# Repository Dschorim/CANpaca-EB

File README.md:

# CANpaca-EB
This is the extruder board from the CANpaca printer board family.

## Features
 - CAN input (with 7.5A@24V) input
 - 1 extrudder stepper (via tmc2130 with SPI control)
 - 2 PWM fans
 - support for klicky probe / bltouch
 - 1 hotend
 - 1 regular thermistor
 - 1 thermistor via MAX31865
 - ADXL345 Accererometer
 - runout sensor
 - RGB lighting

## Changelog

### V0.2
 - changed caps from 0603 to 0402
 - changed resistors from 0603 to 0402
 - decoupling caps are now properly placed close to power pins
 - added thermal vias below rp2040
 - increased via diameter from 0.4mm to 0.45mm to save cost
 - changed to hardware SPI pins

### V0.1
 - initial release

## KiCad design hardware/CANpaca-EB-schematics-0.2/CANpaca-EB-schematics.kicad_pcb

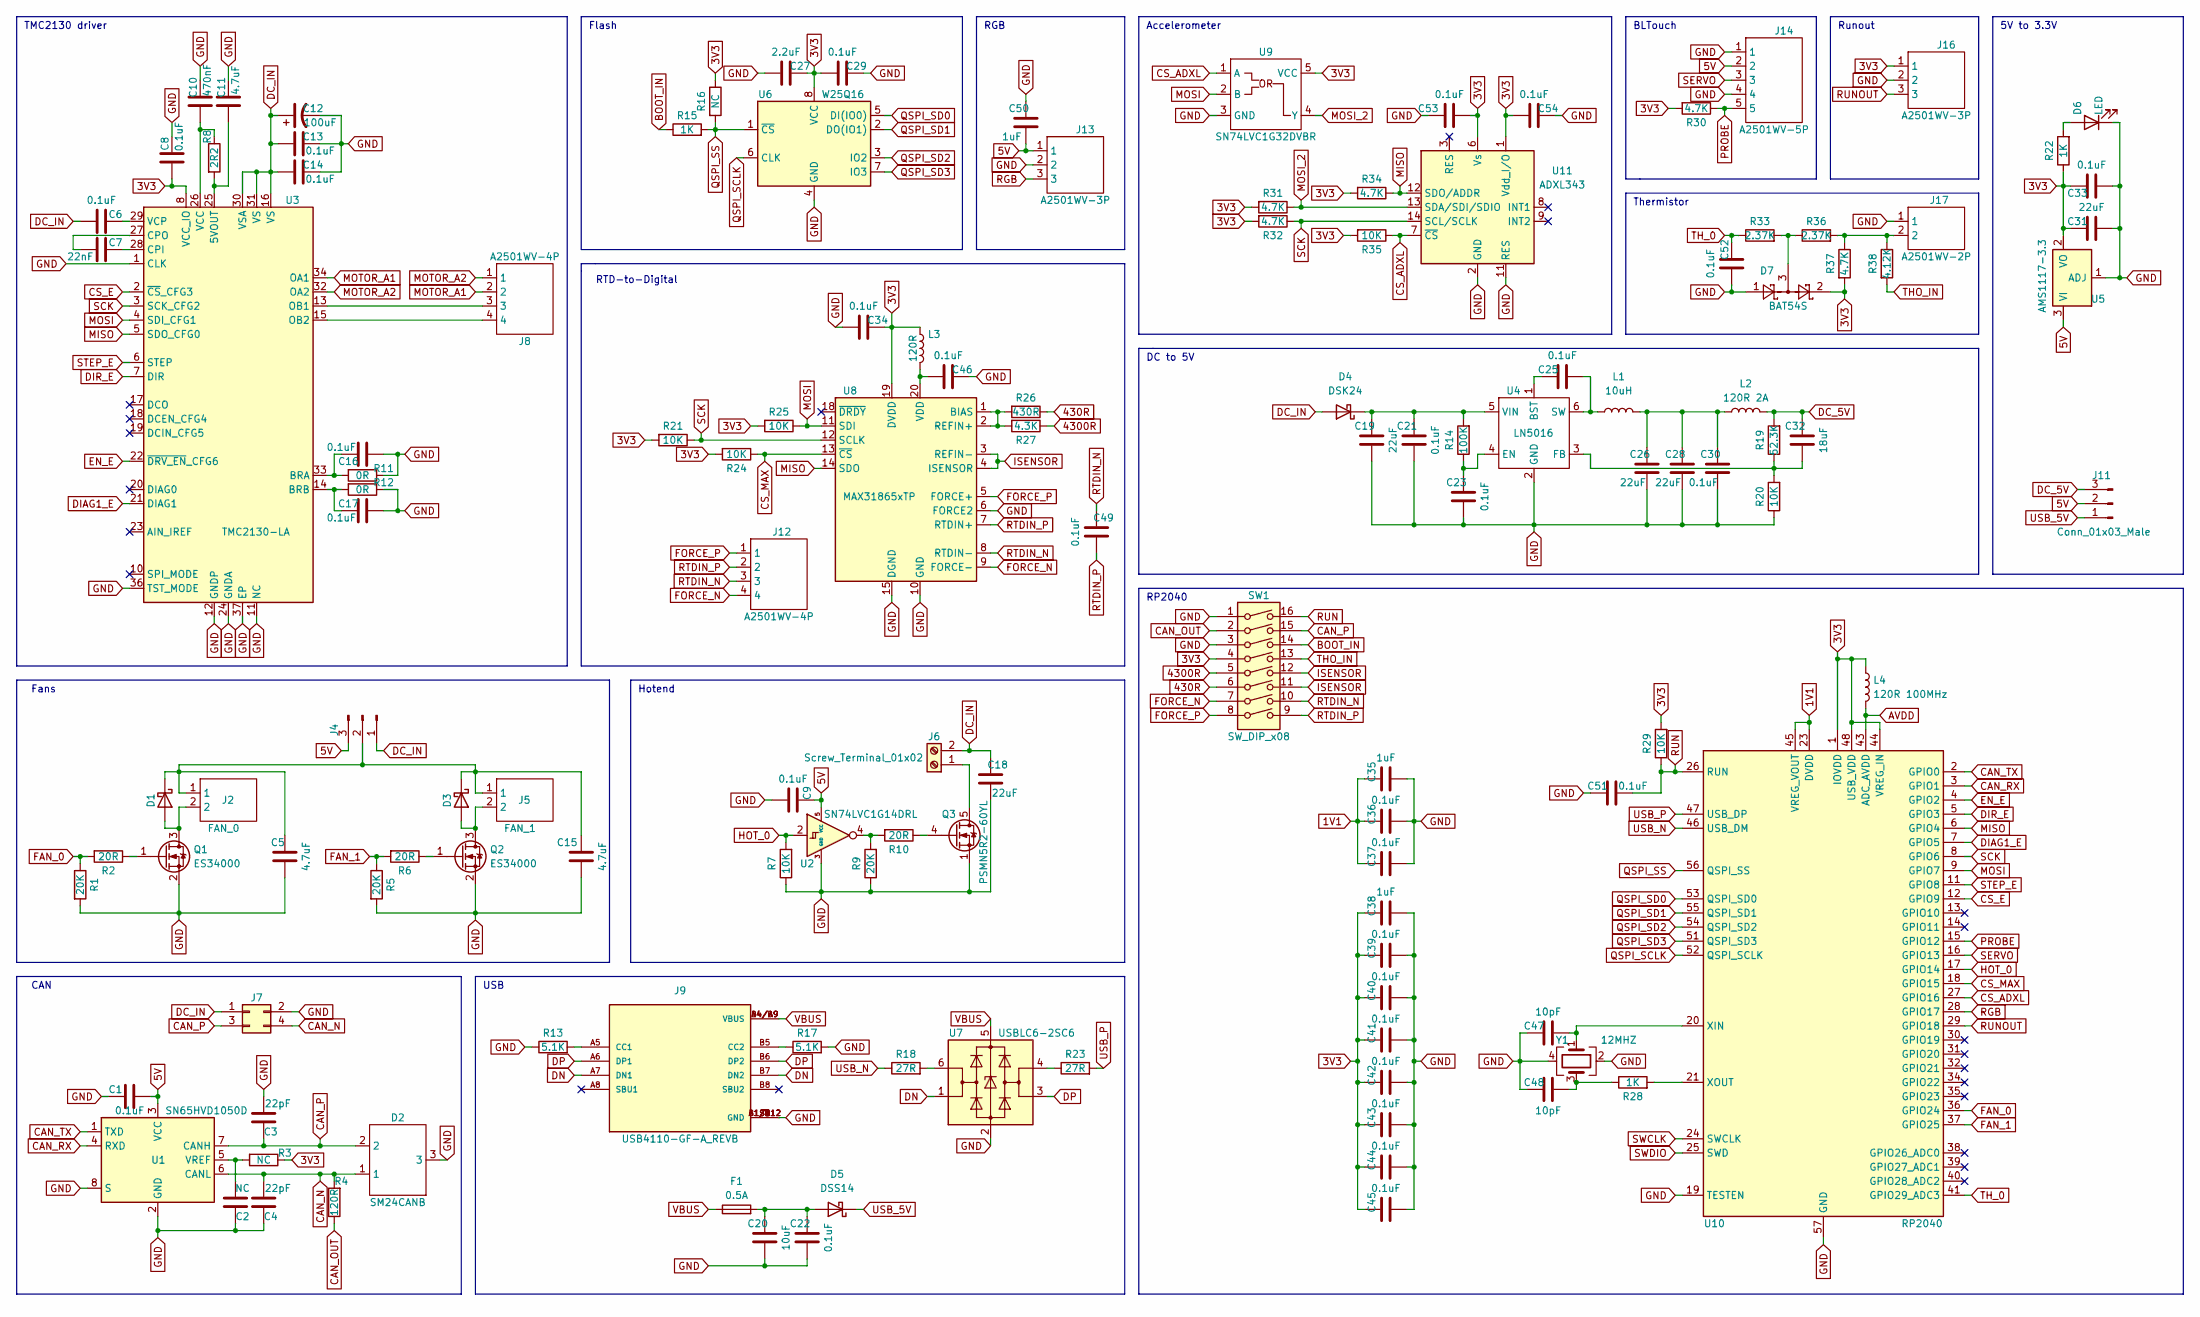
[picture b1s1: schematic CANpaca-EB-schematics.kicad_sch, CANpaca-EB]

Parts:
C1, C6, C8, C9, C13, C14, C16, C17, C21, C22, C23, C25, C29, C30, C33, C34, C36, C37, C39, C40, C41, C42, C43, C44, C45, C46, C49, C51, C52, C53, C54: 0.1uF; C_0402_1005Metric
C2: NC; C_0402_1005Metric
C3, C4: 22pF; C_0402_1005Metric
C5, C11, C15: 4.7uF; C_0402_1005Metric
C7: 22nF; C_0402_1005Metric
C10: 470nF; C_0402_1005Metric
C12: 100uF; CP_Elec_10x14.3
C18, C19, C26, C28, C31: 22uF; C_0402_1005Metric
C20: 10uF; C_0402_1005Metric
C27: 2.2uF; C_0402_1005Metric
C32: 18uF; C_0402_1005Metric
C35, C38, C50: 1uF; C_0402_1005Metric
C47, C48: 10pF; C_0402_1005Metric
D1, D3: D_Schottky; D_SOD-323
D2: SM24CANB; SOT-23
D4: DSK24; D_SOD-123
D5: DSS14; D_SOD-123F
D6: LED; LED_0603_1608Metric
D7: BAT54S; SOT-23
F1: 0.5A; Fuse_BelFuse_0ZRE0005FF_L8.3mm_W3.8mm
J2: FAN_0; A2501WV-2P
J4, J11: Conn_01x03_Male; PinHeader_1x03_P2.54mm_Vertical
J5: FAN_1; A2501WV-2P
J6: Screw_Terminal_01x02; KF350-2P
J7: Conn_02x02_Odd_Even; Molex_Micro-Fit_3.0_43045-0400_2x02_P3.00mm_Horizontal
J8: A2501WV-4P
J9: USB4110-GF-A_REVB; GCT_USB4110-GF-A_REVB; PARTREV B
J12: A2501WV-4P; A1250WV-4P
J13, J16: A2501WV-3P; A1250WV-3P
J14: A2501WV-5P; A1250WV-5P
J17: A2501WV-2P
L1: 10uH; L_0603_1608Metric
L2: 120R 2A; L_0805_2012Metric
L3: 120R; L_0805_2012Metric
L4: 120R 100MHz; L_0603_1608Metric
Q1, Q2: ES34000; SOT-23
Q3: PSMN5R2-60YL; LFPAK56
R1, R5, R9: 20K; R_0402_1005Metric
R2, R6, R10: 20R; R_0402_1005Metric
R3, R16: NC; R_0402_1005Metric
R4: 120R; R_0402_1005Metric
R7, R20, R21, R24, R25, R29, R35: 10K; R_0402_1005Metric
R8: 2R2; R_0402_1005Metric
R11, R12: 0R; R_0402_1005Metric
R13, R17: 5.1K; R_0402_1005Metric
R14: 100K; R_0402_1005Metric
R15, R22, R28: 1K; R_0402_1005Metric
R18, R23: 27R; R_0402_1005Metric
R19: 52.3K; R_0402_1005Metric
R26: 430R; R_0402_1005Metric
R27: 4.3K; R_0402_1005Metric
R30, R31, R32, R34, R37: 4.7K; R_0402_1005Metric
R33, R36: 2.37K; R_0402_1005Metric
R38: 4.12K; R_0402_1005Metric
SW1: SW_DIP_x08; SW_DIP_SPSTx08_Slide_Copal_CHS-08B_W7.62mm_P1.27mm
U1: SN65HVD1050D; SOIC-8_3.9x4.9mm_P1.27mm
U2: SN74LVC1G14DRL; SOT-553
U3: TMC2130-LA; QFN-36-1EP_5x6mm_P0.5mm_EP3.6x4.1mm
U4: LN5016; SOT-23-6
U5: AMS1117-3.3; SOT-223-3_TabPin2
U6: W25Q16; SOIC-8_3.9x4.9mm_P1.27mm
U7: USBLC6-2SC6; SOT-23-6
U8: MAX31865xTP; TQFN-20-1EP_5x5mm_P0.65mm_EP3.25x3.25mm
U9: SN74LVC1G32DVBR; SOT-23-5
U10: RP2040; QFN-56-1EP_7x7mm_P0.4mm_EP3.2x3.2mm
U11: ADXL343; LGA-14_3x5mm_P0.8mm_LayoutBorder1x6y
Y1: 12MHZ; Crystal_SMD_3225-4Pin_3.2x2.5mm

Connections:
1V1: C35.2, C36.2, C37.2, U10.23 (DVDD), U10.45 (VREG_VOUT), U10.50 (DVDD)
3V3: C8.2, C27.1, C29.2, C31.2, C33.2, C34.1, C38.2, C39.2, C40.2, C41.2, C42.2, C43.2, C44.2, C45.2, C53.1, C54.2, D7.2, J16.1, L3.1, L4.1, R3.1, R16.1, R21.2, R22.1, R24.2, R25.2, R29.2, R30.2, R31.2, R32.2, R34.2, R35.2, R37.2, SW1.4, U3.8 (VCC_IO), U5.2 (VO), U6.8 (VCC), U8.19 (DVDD), U9.5 (VCC), U10.1 (IOVDD), U10.10 (IOVDD), U10.22 (IOVDD), U10.33 (IOVDD), U10.42 (IOVDD), U10.44 (VREG_IN), U10.48 (USB_VDD), U10.49 (IOVDD), U11.1 (Vdd_I/O), U11.6 (Vs)
5V: C1.2, C9.2, C50.1, J4.3, J11.2, J13.1, J14.2, U1.3 (VCC), U2.5 (VCC), U5.3 (VI)
430R: R26.1, SW1.6
4300R: R27.1, SW1.5
AVDD: L4.2, U10.43 (ADC_AVDD)
BOOT_IN: R15.1, SW1.14
CAN_N: C4.2, D2.1, J7.4, R4.2, U1.6 (CANL)
CAN_OUT: R4.1, SW1.2
CAN_P: C3.1, D2.2, J7.3, SW1.15, U1.7 (CANH)
CAN_RX: U1.4 (RXD), U10.3 (GPIO1)
CAN_TX: U1.1 (TXD), U10.2 (GPIO0)
CS_ADXL: R35.1, U9.1 (A), U10.27 (GPIO16), U11.7 (~CS)
CS_E: U3.2 (~CS_CFG3), U10.12 (GPIO9)
CS_MAX: R24.1, U8.13 (~CS), U10.18 (GPIO15)
DC_5V: C32.2, J11.3, L2.2, R19.2
DC_IN: C6.1, C12.1, C13.2, C14.2, C18.2, D4.2 (A), J4.1, J6.2, J7.1, U3.16 (VS), U3.30 (VSA), U3.31 (VS)
DIAG1_E: U3.21 (DIAG1), U10.7 (GPIO5)
DIR_E: U3.7 (DIR), U10.5 (GPIO3)
DN: J9.A7 (DN1), J9.B7 (DN2), U7.1 (I/O1)
DP: J9.A6 (DP1), J9.B6 (DP2), U7.3 (I/O2)
EN_E: U3.22 (~DRV_EN_CFG6), U10.4 (GPIO2)
FAN_0: R1.1, R2.2, U10.36 (GPIO24)
FAN_1: R5.1, R6.2, U10.37 (GPIO25)
FORCE_N: J12.4, SW1.7, U8.9 (FORCE-)
FORCE_P: J12.1, SW1.8, U8.5 (FORCE+)
GND: C1.1, C2.1, C3.2, C4.1, C5.1, C8.1, C9.1, C10.1, C11.1, C12.2, C13.1, C14.1, C15.1, C16.2, C17.2, C18.1, C19.1, C20.1, C21.1, C22.1, C23.1, C26.1, C27.2, C28.1, C29.1, C30.1, C31.1, C33.1, C34.2, C35.1, C36.1, C37.1, C38.1, C39.1, C40.1, C41.1, C42.1, C43.1, C44.1, C45.1, C46.1, C47.1, C48.1, C50.2, C51.1, C52.2, C53.2, C54.1, D2.3, D6.1 (K), D7.1, J7.2, J9.A1/B12 (GND), J9.B1/A12 (GND), J9.S1 (GND), J9.S2 (GND), J9.S3 (GND), J9.S4 (GND), J13.2, J14.1, J14.4, J16.2, J17.1, Q1.2 (S), Q2.2 (S), Q3.1 (S), Q3.2 (S), Q3.3 (S), R1.2, R5.2, R7.1, R9.1, R11.1, R12.1, R13.1, R17.2, R20.1, SW1.1, SW1.3, U1.2 (GND), U1.8 (S), U2.3 (GND), U3.1 (CLK), U3.11 (NC), U3.12 (GNDP), U3.24 (GNDA), U3.35 (GNDP), U3.36 (TST_MODE), U3.37 (EP), U4.2 (GND), U5.1 (ADJ), U6.4 (GND), U7.2 (GND), U8.6 (FORCE2), U8.10 (GND), U8.15 (DGND), U8.16 (GND), U8.21 (GND), U9.3 (GND), U10.19 (TESTEN), U10.57 (GND), U11.2 (GND), U11.4 (GND), U11.5 (GND), U11.11 (RES), Y1.2, Y1.4
HOT_0: R7.2, U2.2, U10.17 (GPIO14)
ISENSOR: SW1.11, SW1.12, U8.3 (REFIN-), U8.4 (ISENSOR)
MISO: R34.1, U3.5 (SDO_CFG0), U8.14 (SDO), U10.6 (GPIO4), U11.12 (SDO/ADDR)
MOSI: R25.1, U3.4 (SDI_CFG1), U8.11 (SDI), U9.2 (B), U10.9 (GPIO7)
MOSI_2: R31.1, U9.4 (Y), U11.13 (SDA/SDI/SDIO)
MOTOR_A1: J8.2, U3.34 (OA1)
MOTOR_A2: J8.1, U3.32 (OA2)
unnamed: C2.2, R3.2, U1.5 (VREF)
unnamed: C6.2, U3.29 (VCP)
unnamed: C7.1, U3.27 (CPO)
unnamed: C7.2, U3.28 (CPI)
unnamed: C10.2, R8.1, U3.26 (VCC)
unnamed: C11.2, R8.2, U3.25 (5VOUT)
unnamed: C5.2, C15.2, D1.1 (K), D3.1 (K), J2.1, J4.2, J5.1
unnamed: C16.1, R11.2, U3.33 (BRA)
unnamed: C17.1, R12.2, U3.14 (BRB)
unnamed: C19.2, C21.2, D4.1 (K), R14.2, U4.5 (VIN)
unnamed: C20.2, C22.2, D5.2 (A), F1.2
unnamed: C23.2, R14.1, U4.4 (EN)
unnamed: C25.1, L1.1, U4.6 (SW)
unnamed: C25.2, U4.1 (BST)
unnamed: C26.2, C28.2, C30.2, L1.2, L2.1
unnamed: C32.1, R19.1, R20.2, U4.3 (FB)
unnamed: C46.2, L3.2, U8.20 (VDD)
unnamed: C47.2, U10.20 (XIN), Y1.1
unnamed: C48.2, R28.1, Y1.3
unnamed: D1.2 (A), J2.2, Q1.3 (D)
unnamed: D3.2 (A), J5.2, Q2.3 (D)
unnamed: D6.2 (A), R22.2
unnamed: D7.3, R33.2, R36.1
unnamed: J6.1, Q3.5 (D)
unnamed: J8.3, U3.13 (OB1)
unnamed: J8.4, U3.15 (OB2)
unnamed: J9.A5 (CC1), R13.2
unnamed: J9.B5 (CC2), R17.1
unnamed: J17.2, R36.2, R37.1, R38.1
unnamed: Q1.1 (G), R2.1
unnamed: Q2.1 (G), R6.1
unnamed: Q3.4 (G), R10.1
unnamed: R9.2, R10.2, U2.4
unnamed: R18.2, U7.6 (I/O1)
unnamed: R23.1, U7.4 (I/O2)
unnamed: R26.2, R27.2, U8.1 (BIAS), U8.2 (REFIN+)
unnamed: R28.2, U10.21 (XOUT)
PROBE: J14.5, R30.1, U10.15 (GPIO12)
QSPI_SCLK: U6.6 (CLK), U10.52 (QSPI_SCLK)
QSPI_SD0: U6.5 (DI(IO0)), U10.53 (QSPI_SD0)
QSPI_SD1: U6.2 (DO(IO1)), U10.55 (QSPI_SD1)
QSPI_SD2: U6.3 (IO2), U10.54 (QSPI_SD2)
QSPI_SD3: U6.7 (IO3), U10.51 (QSPI_SD3)
QSPI_SS: R15.2, R16.2, U6.1 (~CS), U10.56 (QSPI_SS)
RGB: J13.3, U10.28 (GPIO17)
RTDIN_N: C49.2, J12.3, SW1.10, U8.8 (RTDIN-)
RTDIN_P: C49.1, J12.2, SW1.9, U8.7 (RTDIN+)
RUN: C51.2, R29.1, SW1.16, U10.26 (RUN)
RUNOUT: J16.3, U10.29 (GPIO18)
SCK: R21.1, R32.1, U3.3 (SCK_CFG2), U8.12 (SCLK), U10.8 (GPIO6), U11.14 (SCL/SCLK)
SERVO: J14.3, U10.16 (GPIO13)
STEP_E: U3.6 (STEP), U10.11 (GPIO8)
SWCLK: U10.24 (SWCLK)
SWDIO: U10.25 (SWD)
THO_IN: R38.2, SW1.13
TH_0: C52.1, R33.1, U10.41 (GPIO29_ADC3)
USB_5V: D5.1 (K), J11.1
USB_N: R18.1, U10.46 (USB_DM)
USB_P: R23.2, U10.47 (USB_DP)
VBUS: F1.1, J9.A4/B9 (VBUS), J9.B4/A9 (VBUS), U7.5 (VBUS)

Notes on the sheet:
5V to 3.3V
Fans
TMC2130 driver
Flash
USB
BLTouch
RP2040
Accelerometer
RGB
Runout
Hotend
RTD-to-Digital
Thermistor
CAN
DC to 5V

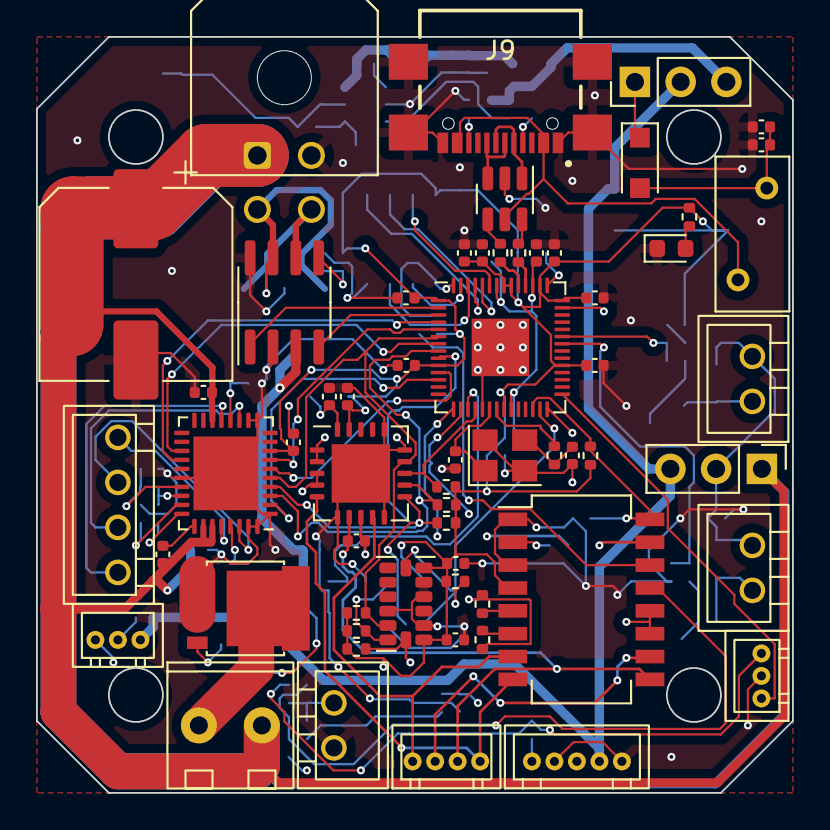
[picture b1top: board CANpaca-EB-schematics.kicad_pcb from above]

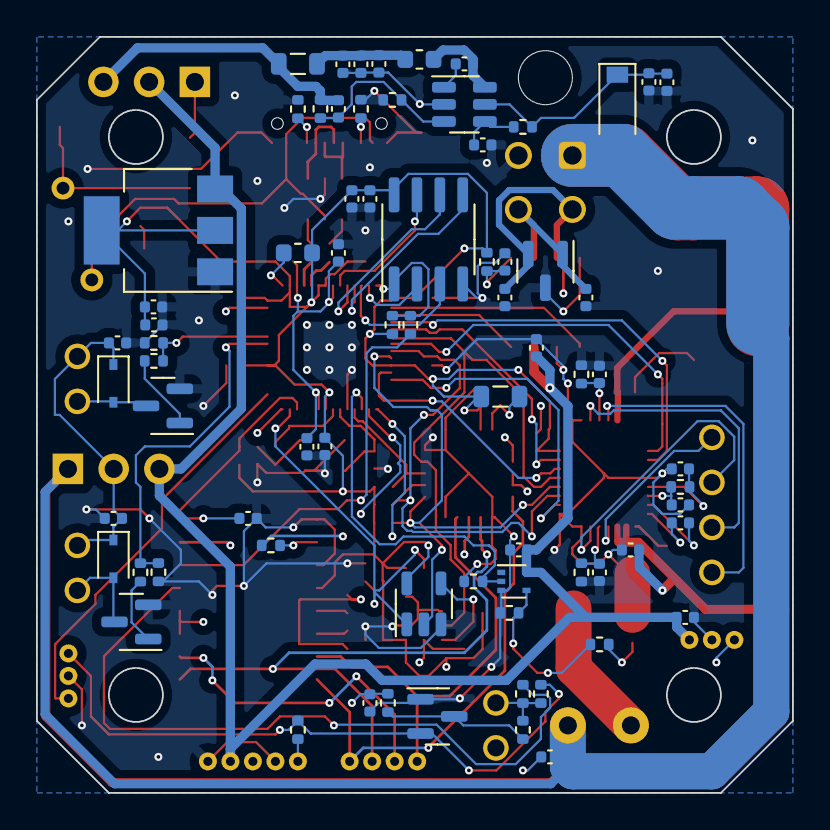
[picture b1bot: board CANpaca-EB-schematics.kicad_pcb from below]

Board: 4 copper layers, 42.0 x 42.0 mm, 132 parts (72 on the bottom side), 92 nets.

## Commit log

2022-09-14 added feature list
2022-09-14 added some schematics
2022-09-14 added CAN interface
2022-09-14 forget to commit this
2022-09-15 more stuff + todo added
2022-09-18 finished schematics
2022-09-20 finished pcb
2022-09-20 more gitignore
2022-09-20 added schematic pdf
2022-09-21 fixed usb resistor
2022-09-21 updated to V0.2
2022-09-21 cleanup
2022-09-21 increased via size
2022-09-21 changed to hardware spi
